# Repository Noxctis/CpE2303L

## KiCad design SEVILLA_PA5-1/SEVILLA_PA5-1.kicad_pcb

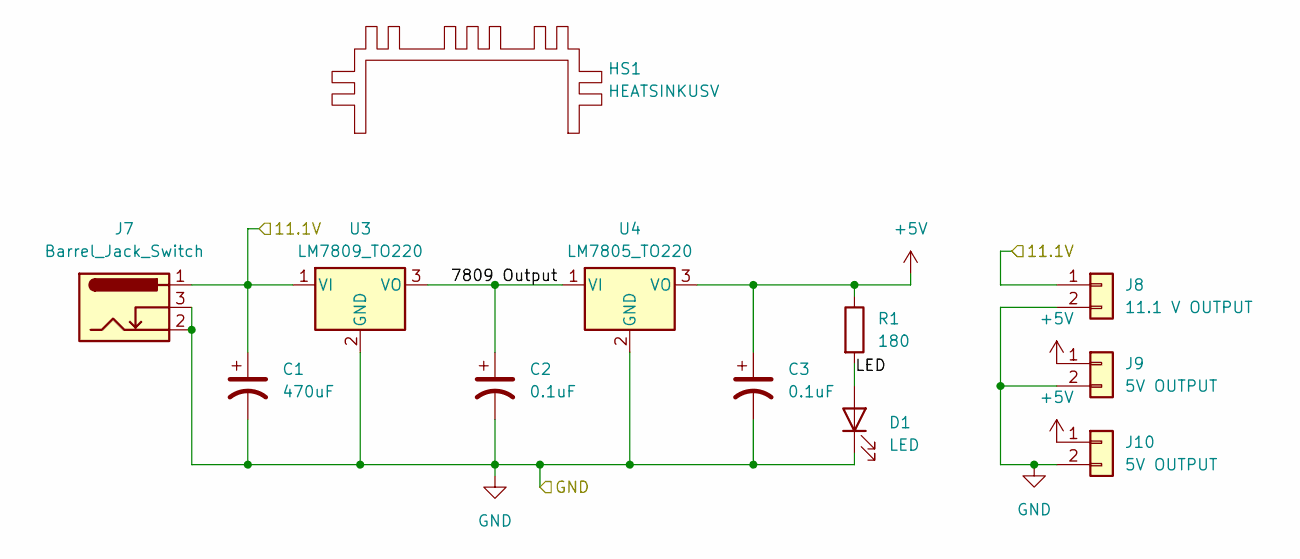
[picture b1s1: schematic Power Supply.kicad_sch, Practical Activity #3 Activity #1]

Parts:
C1: 470uF; CP_Axial_L10.0mm_D4.5mm_P15.00mm_Horizontal
C2, C3: 0.1uF; CP_Axial_L10.0mm_D4.5mm_P15.00mm_Horizontal
D1: LED; LED_D3.0mm
HS1: HEATSINKUSV
J7: Barrel_Jack_Switch; BarrelJack_Horizontal
J8: 11.1 V OUTPUT; PinSocket_1x02_P2.54mm_Vertical
J9, J10: 5V OUTPUT; PinSocket_1x02_P2.54mm_Vertical
R1: 180; R_Axial_DIN0204_L3.6mm_D1.6mm_P5.08mm_Horizontal
U3: LM7809_TO220; TO-220-3_Vertical
U4: LM7805_TO220; TO-220-3_Vertical

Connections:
+5V: C3.1, J9.1, J10.1, R1.1, U4.3 (VO)
/Motor Driver/11.1V: C1.1, J7.1, J8.1, U3.1 (VI); also elsewhere on the board
/Power Supply/7809 Output: C2.1, U3.3 (VO), U4.1 (VI)
/Power Supply/LED: D1.2 (A), R1.2
GND: C1.2, C2.2, C3.2, D1.1 (K), J7.2, J7.3, J8.2, J9.2, J10.2, U3.2 (GND), U4.2 (GND); also elsewhere on the board

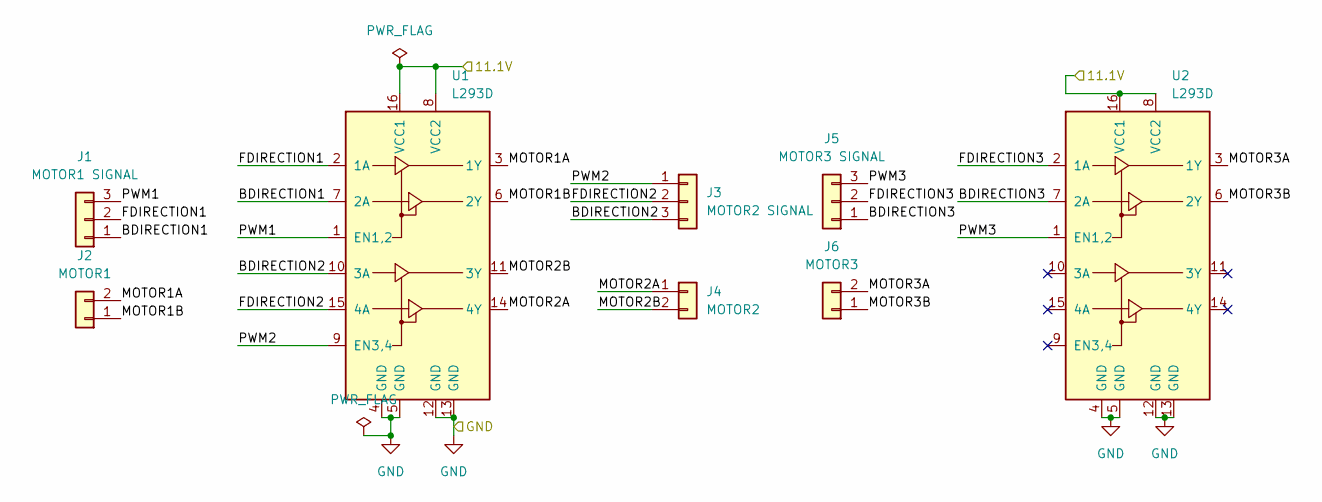
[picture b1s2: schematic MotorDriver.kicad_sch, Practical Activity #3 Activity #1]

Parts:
J1: MOTOR1 SIGNAL; PinSocket_1x03_P2.54mm_Vertical
J2: MOTOR1; PinSocket_1x02_P2.54mm_Vertical
J3: MOTOR2 SIGNAL; PinSocket_1x03_P2.54mm_Vertical
J4: MOTOR2; PinSocket_1x02_P2.54mm_Vertical
J5: MOTOR3 SIGNAL; PinSocket_1x03_P2.54mm_Vertical
J6: MOTOR3; PinSocket_1x02_P2.54mm_Vertical
U1, U2: L293D; DIP-16_W7.62mm

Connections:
/Motor Driver/11.1V: U1.8 (VCC2), U1.16 (VCC1), U2.8 (VCC2), U2.16 (VCC1); also elsewhere on the board
/Motor Driver/BDIRECTION1: J1.1, U1.7 (2A)
/Motor Driver/BDIRECTION2: J3.3, U1.10 (3A)
/Motor Driver/BDIRECTION3: J5.1, U2.7 (2A)
/Motor Driver/FDIRECTION1: J1.2, U1.2 (1A)
/Motor Driver/FDIRECTION2: J3.2, U1.15 (4A)
/Motor Driver/FDIRECTION3: J5.2, U2.2 (1A)
/Motor Driver/MOTOR1A: J2.2, U1.3 (1Y)
/Motor Driver/MOTOR1B: J2.1, U1.6 (2Y)
/Motor Driver/MOTOR2A: J4.1, U1.14 (4Y)
/Motor Driver/MOTOR2B: J4.2, U1.11 (3Y)
/Motor Driver/MOTOR3A: J6.2, U2.3 (1Y)
/Motor Driver/MOTOR3B: J6.1, U2.6 (2Y)
/Motor Driver/PWM1: J1.3, U1.1 (EN1,2)
/Motor Driver/PWM2: J3.1, U1.9 (EN3,4)
/Motor Driver/PWM3: J5.3, U2.1 (EN1,2)
GND: U1.4 (GND), U1.5 (GND), U1.12 (GND), U1.13 (GND), U2.4 (GND), U2.5 (GND), U2.12 (GND), U2.13 (GND); also elsewhere on the board

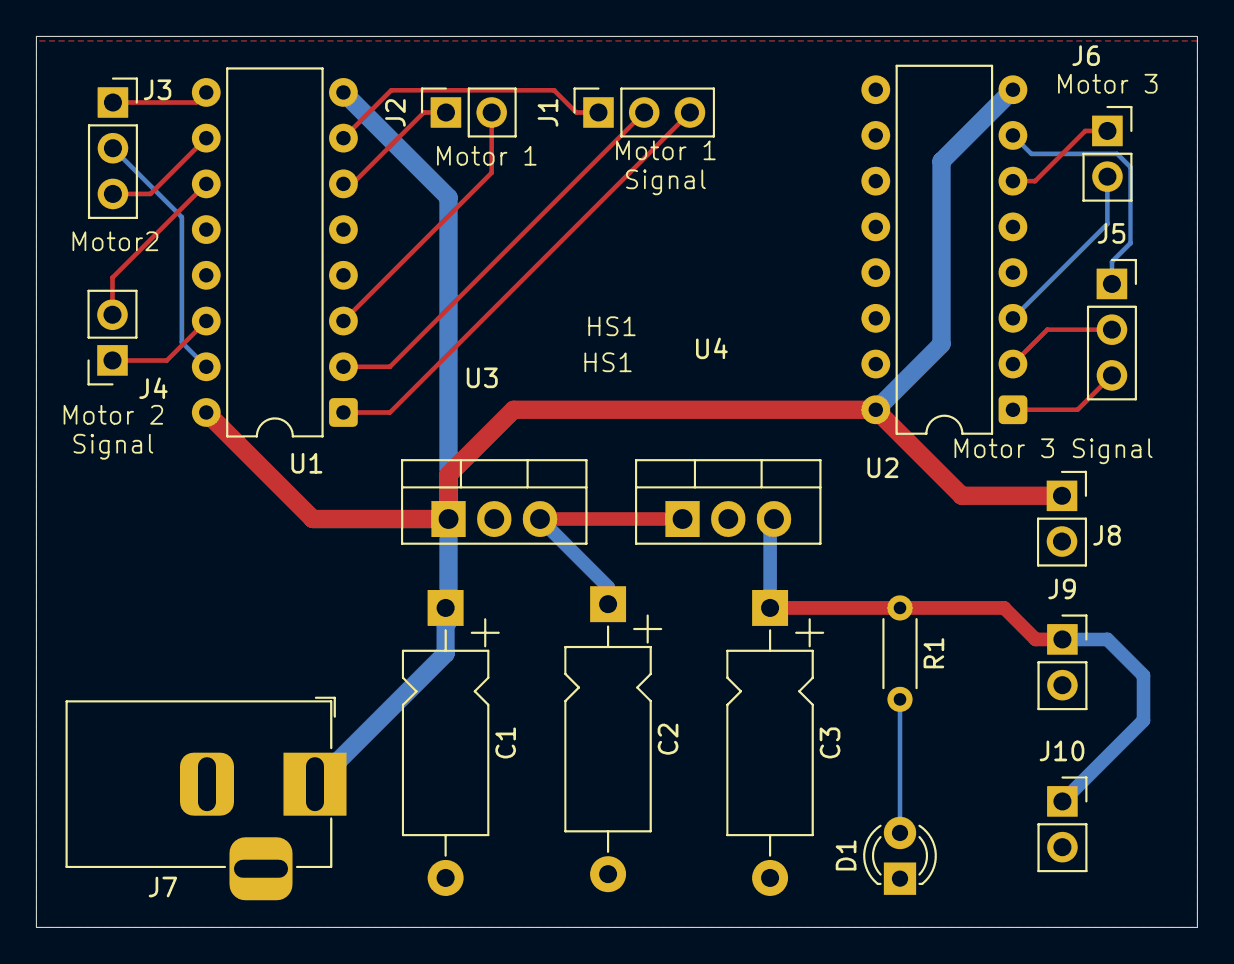
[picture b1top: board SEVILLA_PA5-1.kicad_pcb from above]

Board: 2 copper layers, 64.5 x 49.5 mm, 20 parts (0 on the bottom side), 20 nets.

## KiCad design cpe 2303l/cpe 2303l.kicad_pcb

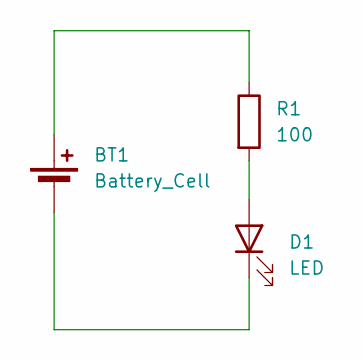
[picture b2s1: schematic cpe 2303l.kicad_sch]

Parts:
BT1: Battery_Cell; BatteryHolder_Keystone_500
D1: LED; LED_D3.0mm_IRBlack
R1: 100; R_Axial_DIN0204_L3.6mm_D1.6mm_P1.90mm_Vertical

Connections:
unnamed: BT1.1 (+), R1.1
unnamed: BT1.2 (-), D1.1 (K)
unnamed: D1.2 (A), R1.2

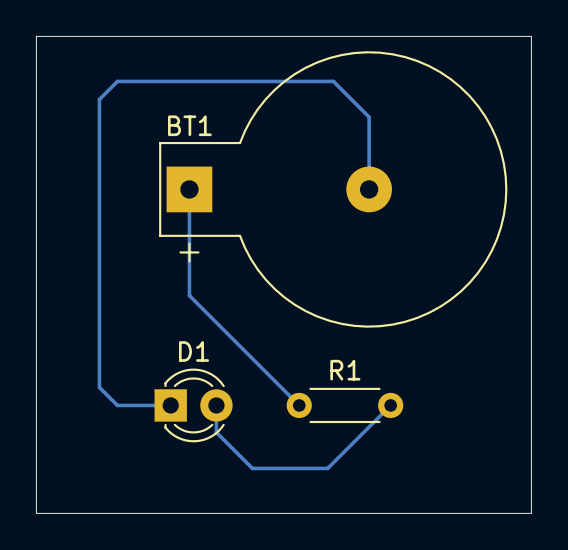
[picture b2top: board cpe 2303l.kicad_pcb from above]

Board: 2 copper layers, 27.5 x 26.5 mm, 3 parts (0 on the bottom side), 3 nets.

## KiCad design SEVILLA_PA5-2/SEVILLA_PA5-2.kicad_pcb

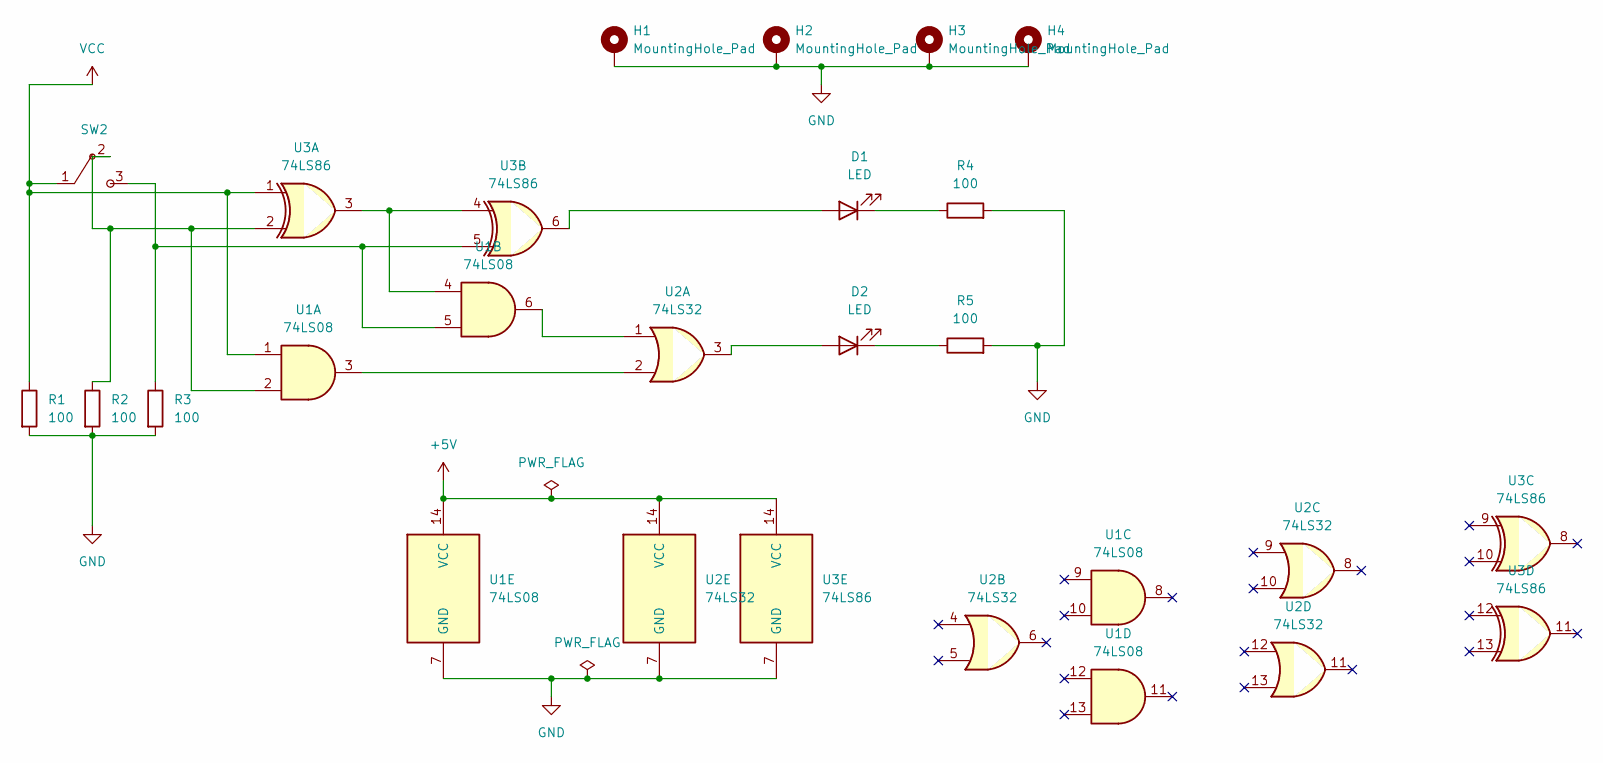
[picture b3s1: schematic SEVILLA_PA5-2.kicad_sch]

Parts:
D1, D2: LED; LED_D3.0mm
H1, H2, H3, H4: MountingHole_Pad; MountingHole_3.2mm_M3_DIN965_Pad
R1, R2, R3, R4, R5: 100; R_Axial_DIN0207_L6.3mm_D2.5mm_P7.62mm_Horizontal
SW2: MSG12ANG03
U1: 74LS08; DIP-14_W7.62mm
U2: 74LS32; DIP-14_W7.62mm
U3: 74LS86; DIP-14_W7.62mm

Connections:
+5V: U1.14 (VCC), U2.14 (VCC), U3.14 (VCC)
GND: H1.1, H2.1, H3.1, H4.1, R1.2, R2.2, R3.2, R4.2, R5.2, U1.7 (GND), U2.7 (GND), U3.7 (GND)
unnamed: D1.2 (A), U3.6
unnamed: D1.1 (K), R4.1
unnamed: D2.2 (A), U2.3
unnamed: D2.1 (K), R5.1
unnamed: R3.1, SW2.3, U1.5, U3.5
unnamed: R2.1, SW2.2, U1.2, U3.2
unnamed: U1.3, U2.2
unnamed: U1.4, U3.3, U3.4
unnamed: U1.6, U2.1
VCC: R1.1, SW2.1, U1.1, U3.1

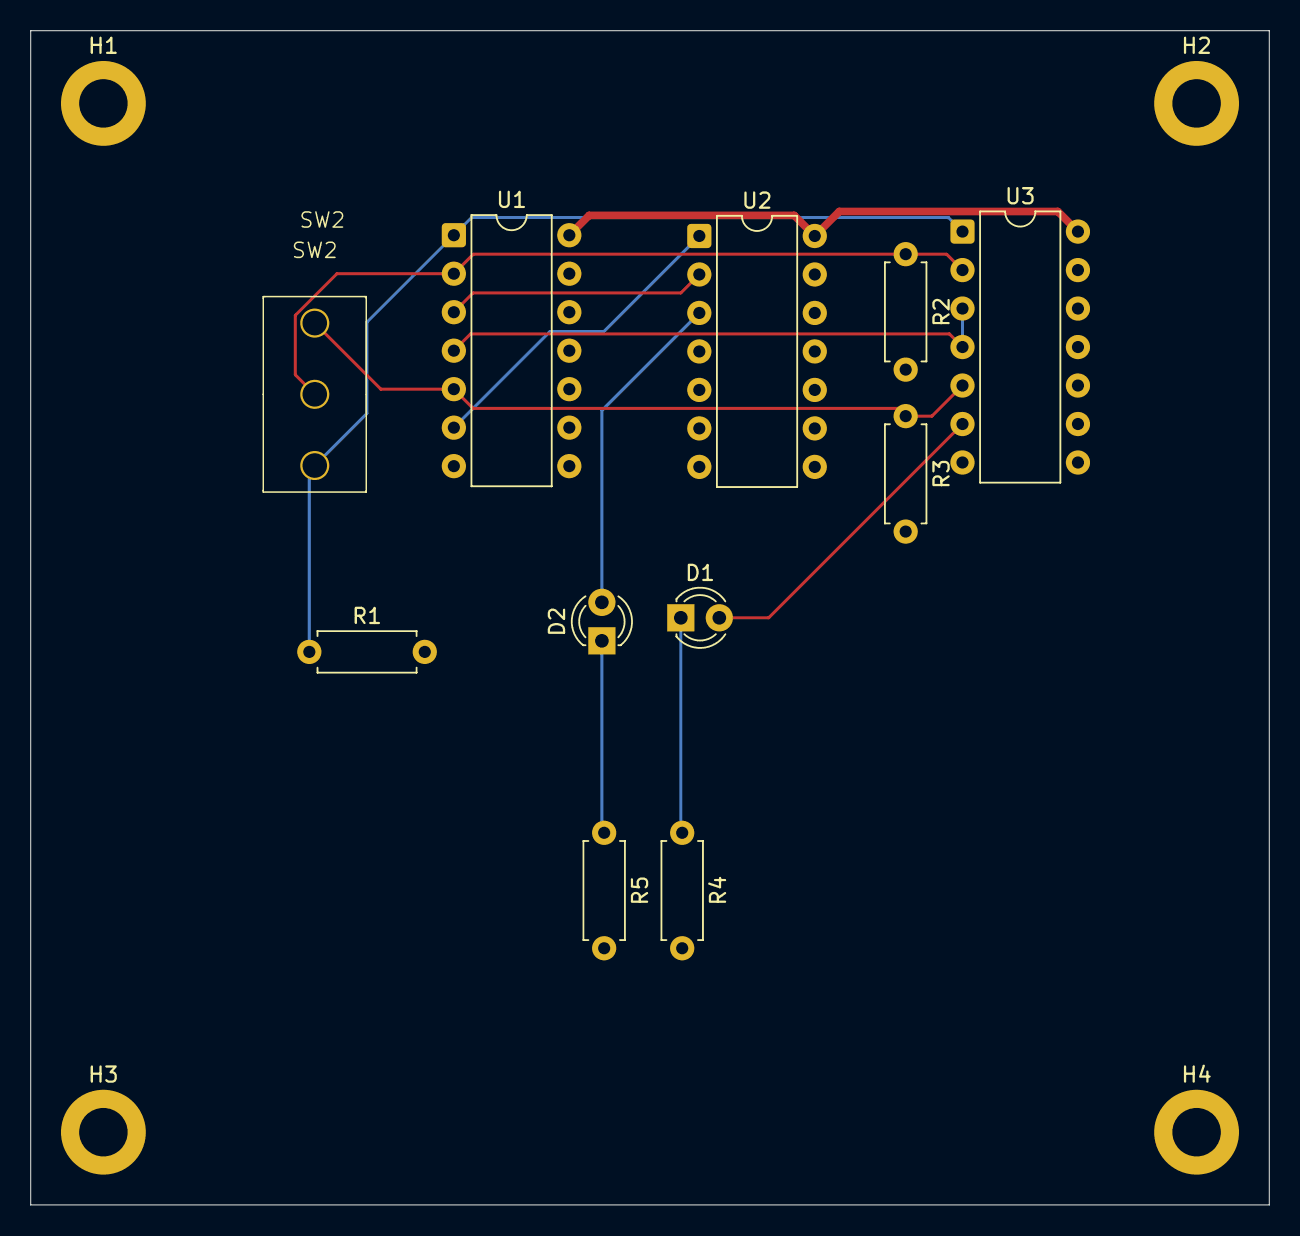
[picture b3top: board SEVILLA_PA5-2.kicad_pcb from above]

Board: 2 copper layers, 81.8 x 77.5 mm, 15 parts (0 on the bottom side), 12 nets.

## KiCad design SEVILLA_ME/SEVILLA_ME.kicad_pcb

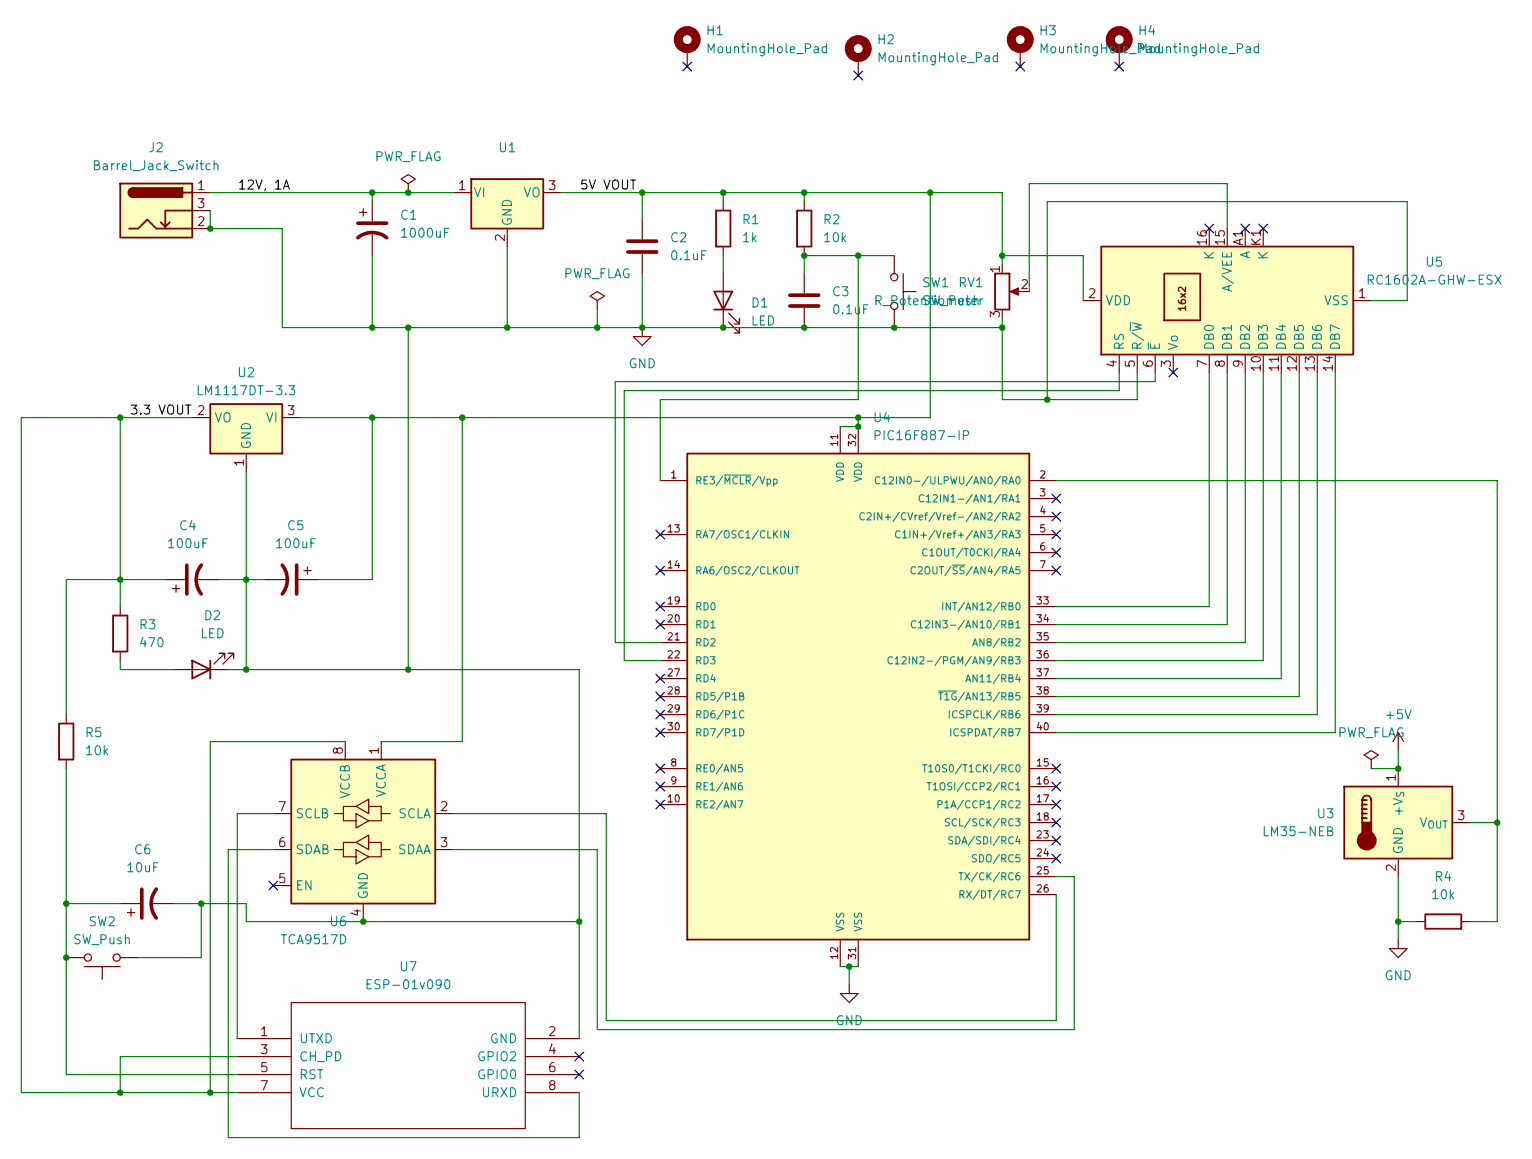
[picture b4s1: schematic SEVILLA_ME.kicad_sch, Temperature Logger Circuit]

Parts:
C1: 1000uF; CP_Axial_L10.0mm_D6.0mm_P15.00mm_Horizontal
C2, C3: 0.1uF; C_Disc_D3.0mm_W2.0mm_P2.50mm
C4, C5: 100uF; CP_Axial_L10.0mm_D4.5mm_P15.00mm_Horizontal
C6: 10uF; CP_Axial_L10.0mm_D6.0mm_P15.00mm_Horizontal
D1, D2: LED; LED_2010_5025Metric_Pad1.52x2.65mm_HandSolder
H1, H2, H3, H4: MountingHole_Pad; MountingHole_3.2mm_M3_DIN965_Pad
J2: Barrel_Jack_Switch; BarrelJack_Horizontal
R1: 1k; R_4020_10251Metric_Pad1.65x5.30mm_HandSolder
R2, R4, R5: 10k; R_4020_10251Metric_Pad1.65x5.30mm_HandSolder
R3: 470; R_4020_10251Metric_Pad1.65x5.30mm_HandSolder
RV1: R_Potentiometer; Potentiometer_ACP_CA6-H2,5_Horizontal
SW1, SW2: SW_Push; SW_PUSH_6mm_H4.3mm
U1: LM7805_TO220; TO-220-3_Vertical
U2: LM1117DT-3.3; TO-252-3_TabPin2
U3: LM35-NEB; TO-220-3_Vertical
U4: PIC16F887-IP; DIP-40_W15.24mm
U5: RC1602A-GHW-ESX; RC1602A
U6: TCA9517D; SOIC-8_3.9x4.9mm_P1.27mm
U7: ESP-01v090; ESP-01

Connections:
+5V: U3.1 (+V_{S})
/3.3 VOUT: C4.1, R3.1, R5.1, U2.2 (VO), U6.8 (VCCB), U7.3 (CH_PD), U7.7 (VCC)
/5V VOUT: C2.1, C5.1, R1.1, R2.1, RV1.1, U1.3 (VO), U2.3 (VI), U4.11 (VDD), U4.32 (VDD), U5.2 (VDD), U6.1 (VCCA)
/12V, 1A: C1.1, J2.1, U1.1 (VI)
GND: C1.2, C2.2, C3.2, C4.2, C5.2, C6.2, D1.1 (K), D2.1 (K), J2.2, J2.3, R4.1, RV1.3, SW1.2, SW2.1, U1.2 (GND), U2.1 (GND), U3.2 (GND), U4.12 (VSS), U4.31 (VSS), U5.1 (VSS), U5.5 (R/~W), U6.4 (GND), U7.2 (GND)
unnamed: D1.2 (A), R1.2
unnamed: D2.2 (A), R3.2
unnamed: R4.2, U3.3 (V_{OUT}), U4.2 (C12IN0-/ULPWU/AN0/RA0)
unnamed: U4.35 (AN8/RB2), U5.9 (DB2)
unnamed: U4.37 (AN11/RB4), U5.11 (DB4)
unnamed: U4.36 (C12IN2-/PGM/AN9/RB3), U5.10 (DB3)
unnamed: U4.34 (C12IN3-/AN10/RB1), U5.8 (DB1)
unnamed: U4.39 (ICSPCLK/RB6), U5.13 (DB6)
unnamed: U4.40 (ICSPDAT/RB7), U5.14 (DB7)
unnamed: U4.33 (INT/AN12/RB0), U5.7 (DB0)
unnamed: U4.21 (RD2), U5.6 (~E)
unnamed: U4.22 (RD3), U5.4 (RS)
unnamed: C3.1, R2.2, SW1.1, U4.1 (RE3/~MCLR/Vpp)
unnamed: U4.26 (RX/DT/RC7), U6.2 (SCLA)
unnamed: U4.25 (TX/CK/RC6), U6.3 (SDAA)
unnamed: U4.38 (~T1G/AN13/RB5), U5.12 (DB5)
unnamed: RV1.2, U5.15 (A/VEE)
unnamed: U6.7 (SCLB), U7.1 (UTXD)
unnamed: U6.6 (SDAB), U7.8 (URXD)
unnamed: C6.1, R5.2, SW2.2, U7.5 (RST)

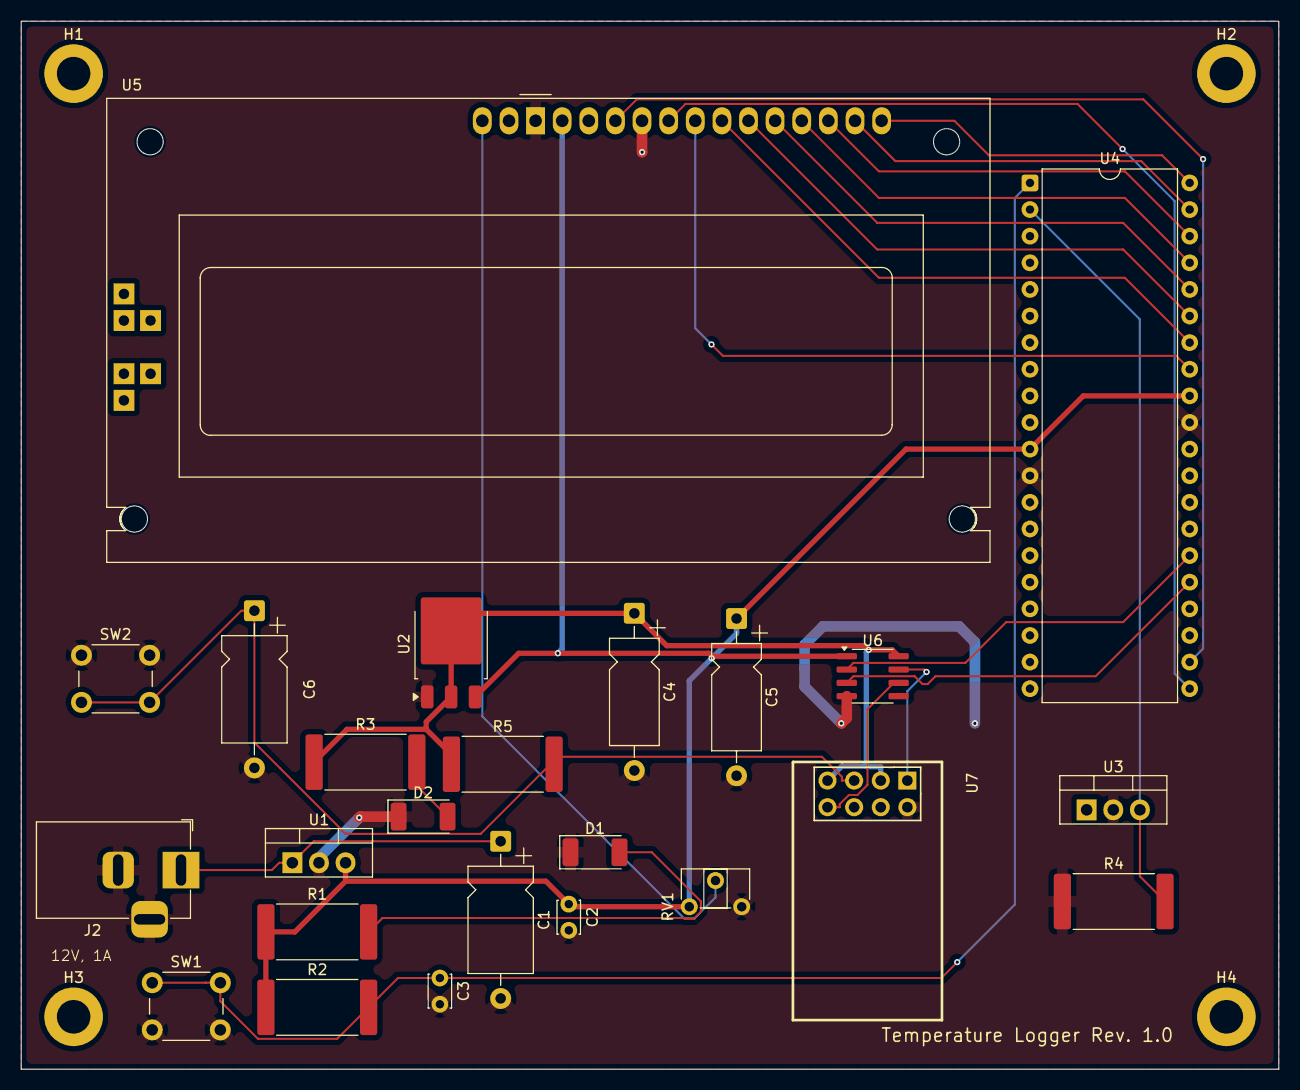
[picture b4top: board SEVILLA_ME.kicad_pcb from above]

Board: 2 copper layers, 120.0 x 100.0 mm, 28 parts (0 on the bottom side), 24 nets.

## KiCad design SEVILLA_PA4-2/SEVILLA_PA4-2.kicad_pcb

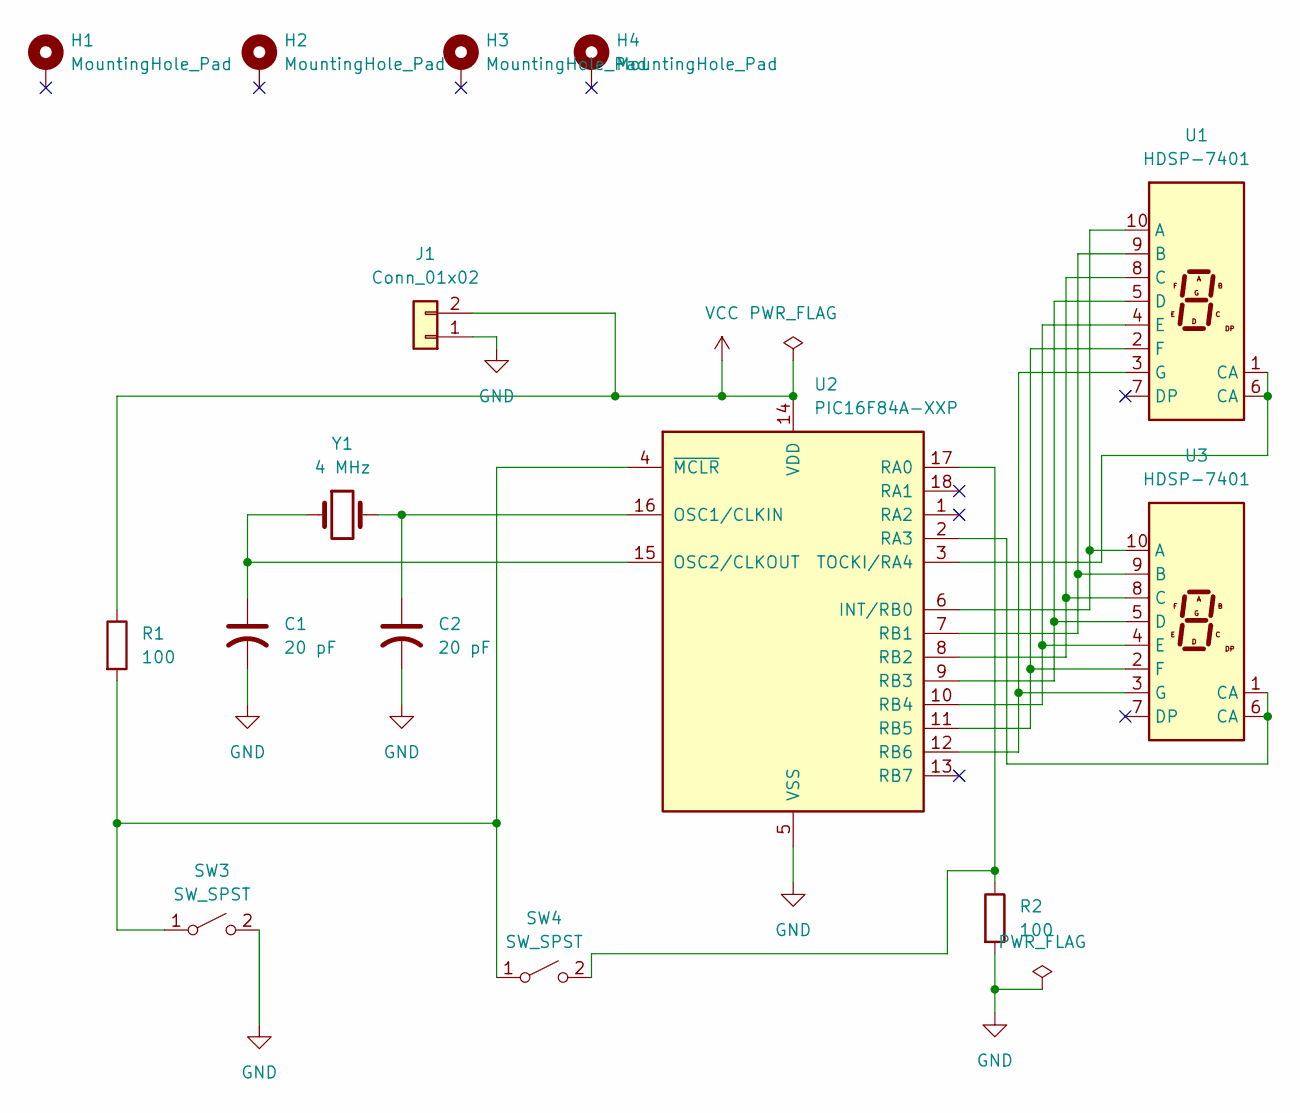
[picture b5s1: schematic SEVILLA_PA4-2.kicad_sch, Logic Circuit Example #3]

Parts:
C1, C2: 20 pF; CP_Axial_L10.0mm_D4.5mm_P15.00mm_Horizontal
H1, H2, H3, H4: MountingHole_Pad; MountingHole_3.2mm_M3_ISO7380_Pad
J1: Conn_01x02; Molex_KK-254_AE-6410-02A_1x02_P2.54mm_Vertical
R1, R2: 100; R_Axial_DIN0204_L3.6mm_D1.6mm_P5.08mm_Horizontal
SW3, SW4: SW_SPST; SW_PUSH_6mm
U1, U3: HDSP-7401
U2: PIC16F84A-XXP; DIP-18_W7.62mm
Y1: 4 MHz; Crystal_HC49-U_Horizontal

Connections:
GND: C1.2, C2.2, H1.1, H2.1, H3.1, H4.1, J1.1, R2.2, SW3.2 (B), U2.5 (VSS)
unnamed: R1.2, SW3.1 (A), SW4.1 (A), U2.4 (~MCLR)
unnamed: R2.1, SW4.2 (B), U2.17 (RA0)
unnamed: U1.10 (A), U2.6 (INT/RB0), U3.10 (A)
unnamed: U1.9 (B), U2.7 (RB1), U3.9 (B)
unnamed: U1.8 (C), U2.8 (RB2), U3.8 (C)
unnamed: U1.5 (D), U2.9 (RB3), U3.5 (D)
unnamed: U1.4 (E), U2.10 (RB4), U3.4 (E)
unnamed: U1.2 (F), U2.11 (RB5), U3.2 (F)
unnamed: U1.3 (G), U2.12 (RB6), U3.3 (G)
unnamed: C2.1, U2.16 (OSC1/CLKIN), Y1.2
unnamed: C1.1, U2.15 (OSC2/CLKOUT), Y1.1
unnamed: U2.2 (RA3), U3.1 (CA), U3.6 (CA)
unnamed: U1.1 (CA), U1.6 (CA), U2.3 (TOCKI/RA4)
VCC: J1.2, R1.1, U2.14 (VDD)

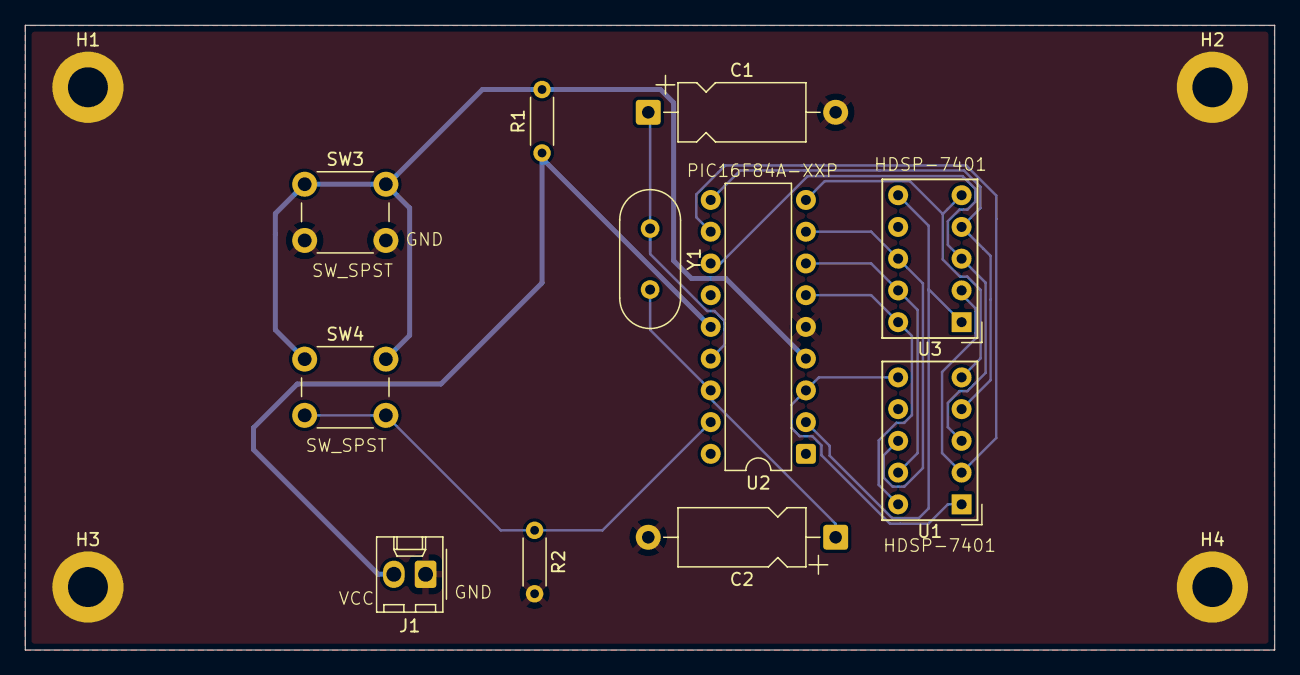
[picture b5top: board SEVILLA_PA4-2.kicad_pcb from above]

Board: 2 copper layers, 100.0 x 50.0 mm, 15 parts (0 on the bottom side), 15 nets.

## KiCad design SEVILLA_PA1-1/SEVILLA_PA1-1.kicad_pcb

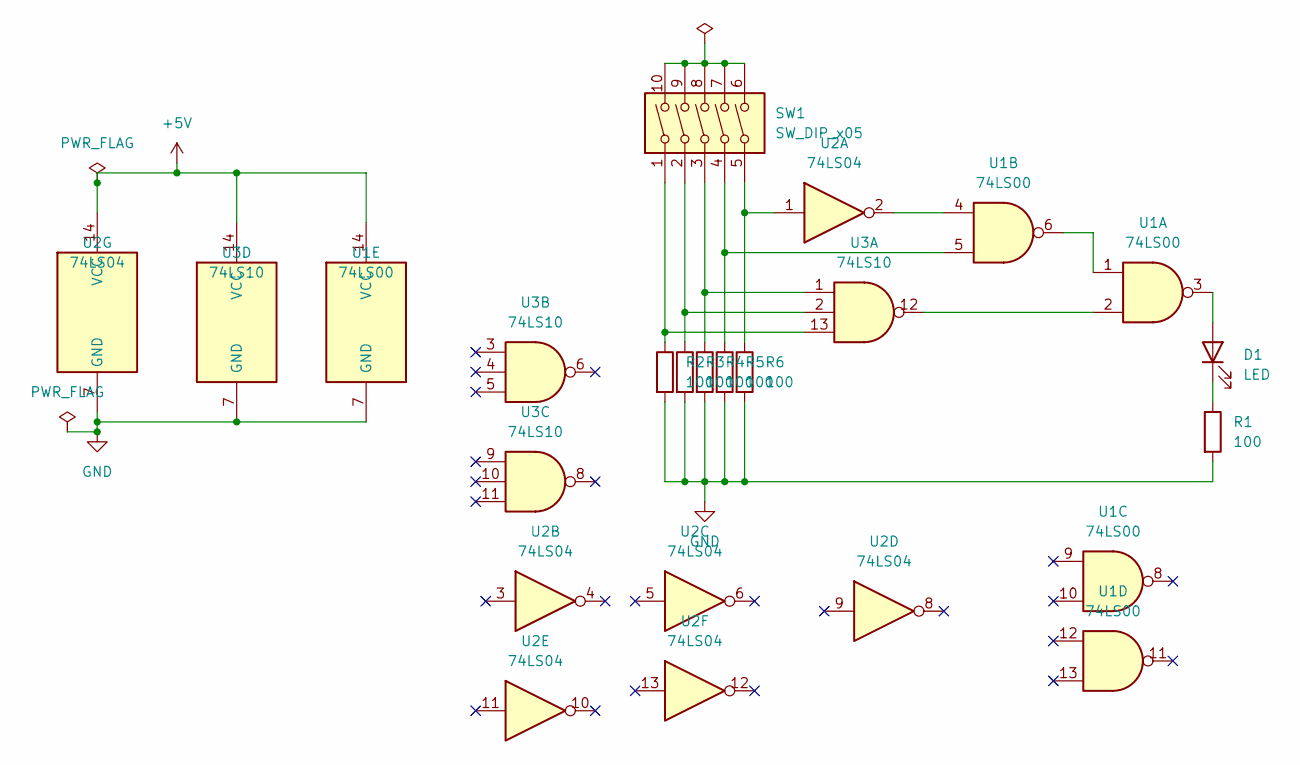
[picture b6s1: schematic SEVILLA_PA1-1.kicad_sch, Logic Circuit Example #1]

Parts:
D1: LED; LED_D1.8mm_W1.8mm_H2.4mm_Horizontal_O1.27mm_Z1.6mm
R1, R2, R3, R4, R5, R6: 100; R_Axial_DIN0204_L3.6mm_D1.6mm_P5.08mm_Horizontal
SW1: SW_DIP_x05; SW_DIP_SPSTx05_Slide_9.78x14.88mm_W7.62mm_P2.54mm
U1: 74LS00; DIP-14_W7.62mm
U2: 74LS04; DIP-14_W7.62mm
U3: 74LS10; DIP-14_W7.62mm

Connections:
+5V: U1.14 (VCC), U2.14 (VCC), U3.14 (VCC)
GND: R1.2, R2.2, R3.2, R4.2, R5.2, R6.2, U1.7 (GND), U2.7 (GND), U3.7 (GND)
unnamed: D1.2 (A), U1.3
unnamed: D1.1 (K), R1.1
unnamed: R2.1, SW1.1, U3.13
unnamed: R3.1, SW1.2, U3.2
unnamed: R4.1, SW1.3, U3.1
unnamed: R5.1, SW1.4, U1.5
unnamed: R6.1, SW1.5, U2.1
unnamed: SW1.6, SW1.7, SW1.8, SW1.9, SW1.10
unnamed: U1.1, U1.6
unnamed: U1.2, U3.12
unnamed: U1.4, U2.2

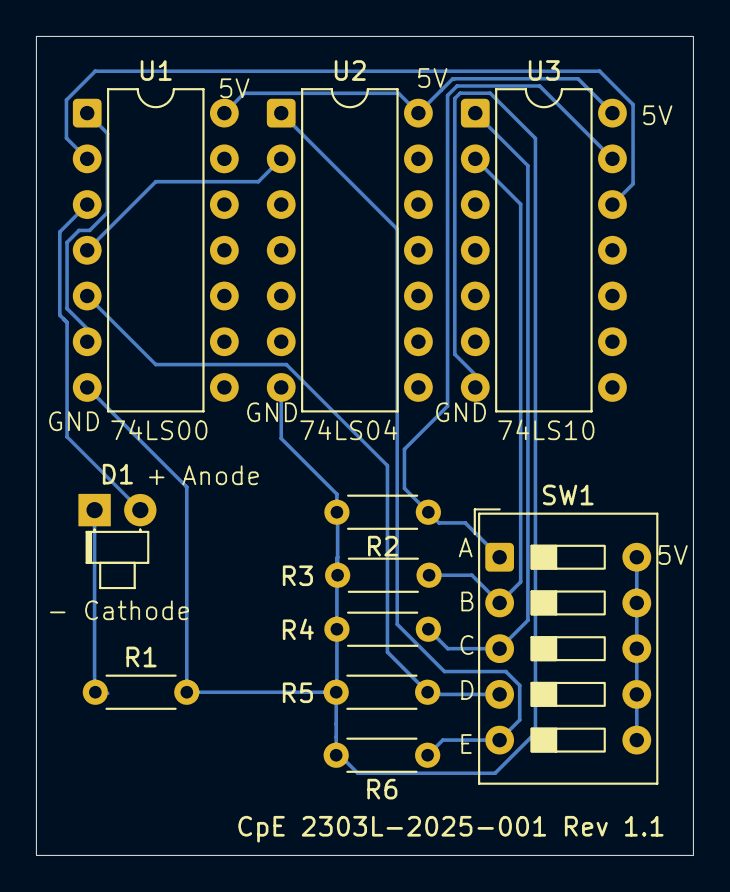
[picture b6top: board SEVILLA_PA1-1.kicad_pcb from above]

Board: 2 copper layers, 36.5 x 45.5 mm, 11 parts (0 on the bottom side), 13 nets.

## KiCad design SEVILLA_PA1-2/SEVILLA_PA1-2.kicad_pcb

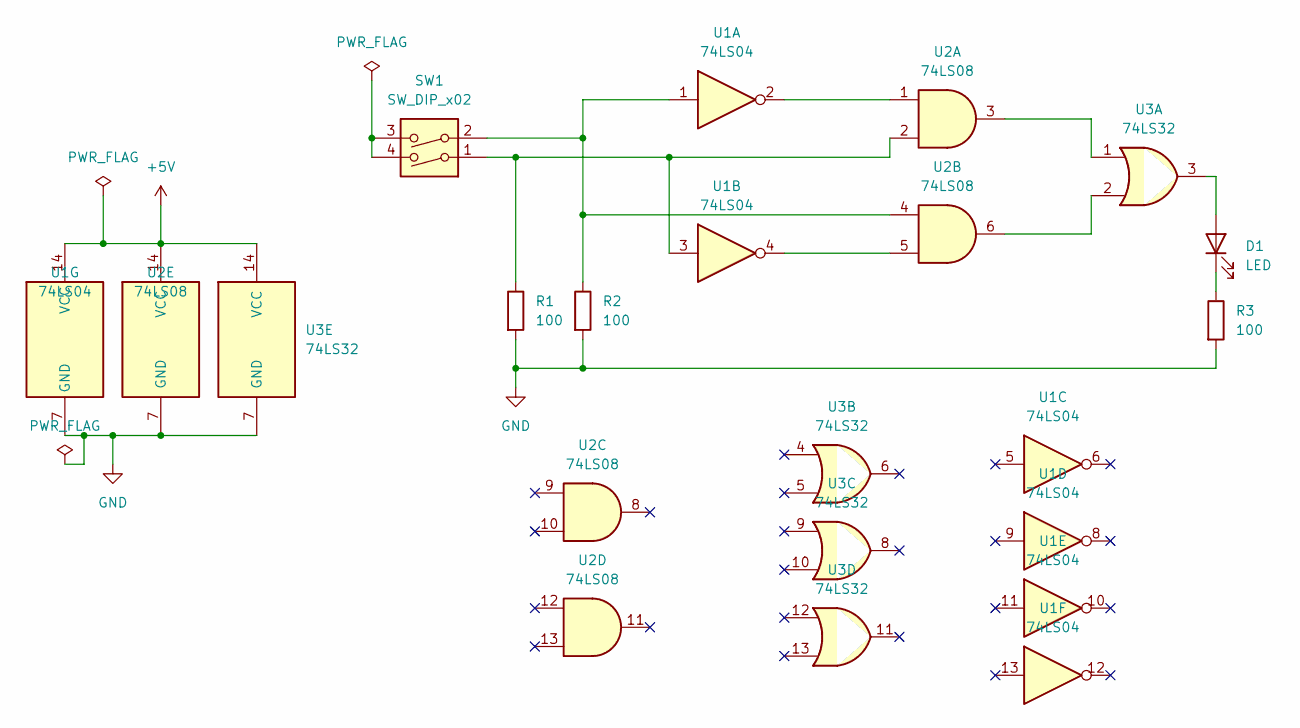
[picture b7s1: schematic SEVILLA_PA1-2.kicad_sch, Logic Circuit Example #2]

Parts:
D1: LED; LED_D1.8mm_W1.8mm_H2.4mm_Horizontal_O6.35mm_Z8.2mm
R1, R2, R3: 100; R_Axial_DIN0204_L3.6mm_D1.6mm_P5.08mm_Horizontal
SW1: SW_DIP_x02; SW_DIP_SPSTx02_Slide_9.78x7.26mm_W7.62mm_P2.54mm
U1: 74LS04; DIP-14_W7.62mm
U2: 74LS08; DIP-14_W7.62mm
U3: 74LS32; DIP-14_W7.62mm

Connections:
+5V: U1.14 (VCC), U2.14 (VCC), U3.14 (VCC)
GND: R1.2, R2.2, R3.2, U1.7 (GND), U2.7 (GND), U3.7 (GND)
unnamed: D1.2 (A), U3.3
unnamed: D1.1 (K), R3.1
unnamed: R1.1, SW1.1, U1.3, U2.2
unnamed: R2.1, SW1.2, U1.1, U2.4
unnamed: SW1.3, SW1.4
unnamed: U1.2, U2.1
unnamed: U1.4, U2.5
unnamed: U2.3, U3.1
unnamed: U2.6, U3.2

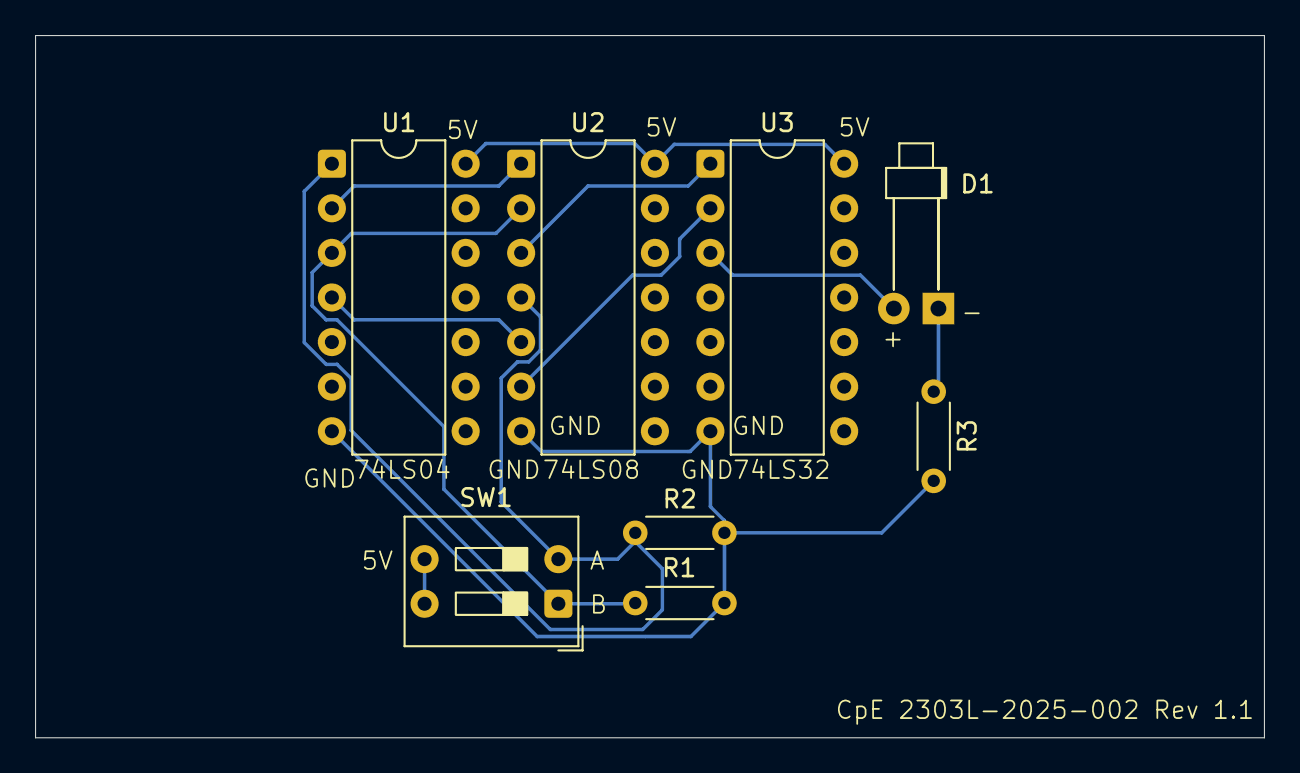
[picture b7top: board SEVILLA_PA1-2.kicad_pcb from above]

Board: 2 copper layers, 70.0 x 40.0 mm, 8 parts (0 on the bottom side), 11 nets.

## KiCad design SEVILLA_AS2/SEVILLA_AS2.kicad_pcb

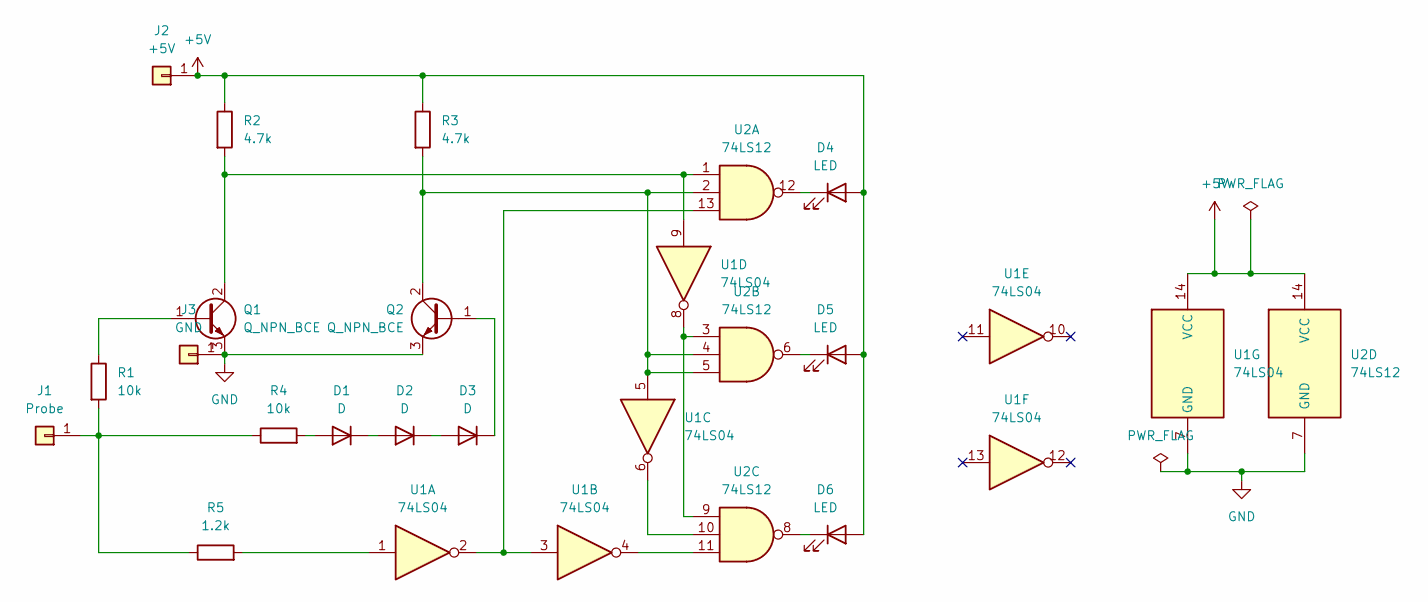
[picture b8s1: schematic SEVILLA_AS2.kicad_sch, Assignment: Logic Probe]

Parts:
D1, D2, D3: D; D_5W_P10.16mm_Horizontal
D4, D5, D6: LED; LED_D5.0mm
J1: Probe; PinSocket_1x01_P2.54mm_Vertical
J2: +5V; PinSocket_1x01_P2.54mm_Vertical
J3: GND; PinSocket_1x01_P2.54mm_Vertical
Q1, Q2: Q_NPN_BCE; TO-92
R1, R4: 10k; R_Axial_DIN0204_L3.6mm_D1.6mm_P5.08mm_Horizontal
R2, R3: 4.7k; R_Axial_DIN0204_L3.6mm_D1.6mm_P5.08mm_Horizontal
R5: 1.2k; R_Axial_DIN0204_L3.6mm_D1.6mm_P5.08mm_Horizontal
U1: 74LS04; DIP-14_W7.62mm
U2: 74LS12; DIP-14_W7.62mm

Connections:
+5V: D4.2 (A), D5.2 (A), D6.2 (A), J2.1, R2.1, R3.1, U1.14 (VCC), U2.14 (VCC)
GND: J3.1, Q1.3 (E), Q2.3 (E), U1.7 (GND), U2.7 (GND)
unnamed: D1.2 (A), R4.2
unnamed: D1.1 (K), D2.2 (A)
unnamed: D2.1 (K), D3.2 (A)
unnamed: D3.1 (K), Q2.1 (B)
unnamed: D4.1 (K), U2.12
unnamed: D5.1 (K), U2.6
unnamed: D6.1 (K), U2.8
unnamed: J1.1, R1.2, R4.1, R5.1
unnamed: Q1.1 (B), R1.1
unnamed: Q1.2 (C), R2.2, U1.9, U2.1
unnamed: Q2.2 (C), R3.2, U1.5, U2.2, U2.4, U2.5
unnamed: R5.2, U1.1
unnamed: U1.2, U1.3, U2.13
unnamed: U1.4, U2.11
unnamed: U1.6, U2.10
unnamed: U1.8, U2.3, U2.9

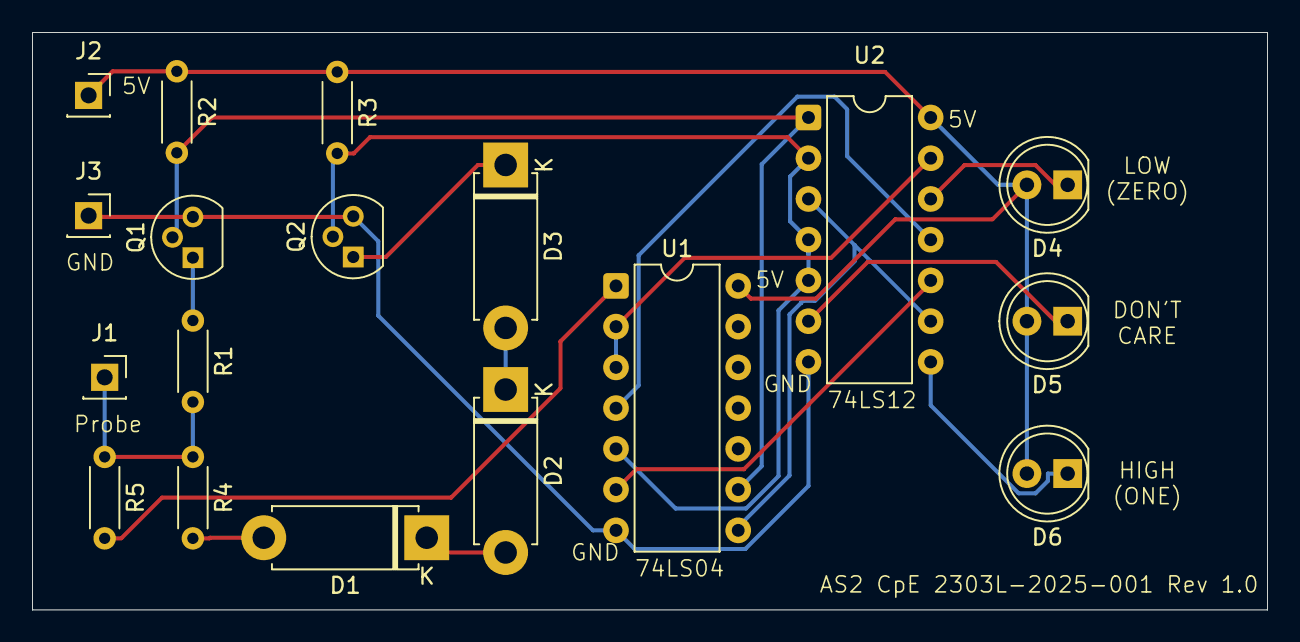
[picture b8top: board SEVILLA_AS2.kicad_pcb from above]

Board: 2 copper layers, 77.0 x 36.0 mm, 18 parts (0 on the bottom side), 18 nets.
